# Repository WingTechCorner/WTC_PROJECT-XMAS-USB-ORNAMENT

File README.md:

# Wing's XMAS Ornament

** ISSUE - Design Seems To produce non-working unit. Investigating... **

* Something for the holidays.
* Made using SMT/SMD components so most/all parts on one side.
* Added header pins on revrse side for adding batteries or different UART(s).
* Added USB-A PCB top to allow plugging into a laptop or computer USB port or to power with a USB-A extension cable.

# JLCPCB Holiday Contest Entry

This is a project I'm also submitting to the [JLCPCB.com](http://www.jlcpcb.com) Holiday Contest!

* http://www.jlcpcb.com

# Hardware

## Components

* CH340G USB-to-TTL interface chip
* AMS1117-3v3 linear voltage regulator
* QMA7981 IMU in I2C mode
* STM32F030F4 - Arm M0 MCU

## STM32 

* 12Mhz External OSC
* Boot0 - CH340G's CTS (pin 9) (pulldown via 4.7K, but can be brought HIGH by CH340G by toggling CTS)

### I2C 

* PA9  - I2C SCL (connects to QMA7981's SCL)
* PA10 - I2C SDA (connects to QMA7981's SDX)
* PB1  - Motion Interrupt Signal ( connects to QMA7981's INT2 )

### UART

* PA2  - UART-TX (connects to CH340G's RX)
* PA3  - UART-RD (connects to CH340G's TX)

### LED Driving Lines

* PA0  - A (CharliePlexed LED Lines)
* PA1  - B (CharliePlexed LED Lines)
* PA4  - C (CharliePlexed LED Lines)
* PA5  - D (CharliePlexed LED Lines)
* PA6  - E (CharliePlexed LED Lines)
* PA7  - F (CharliePlexed LED Lines)
* PA13 - G (CharliePlexed LED Lines)
* PA14 - H (CharliePlexed LED Lines)

## QMA7981

* AD0  - Sets address. Routed to GND for 0. 0x12H
* INT2 - Interrupt signal output. Routed to PB1 on MCU

## CH340G

* TXD  - To MCU RXD
* RXD  - To MCU TXD
* CTS  - To MCU BOOT0 for boot mode selector
* 12Mhz External OSC

# Software

## Building & Installing Arduino Code
The code is setup as a `platformio` project. To build:

```bash
# To compile/build
pio run

# To upload (Note, assumes serial upload)
pio run --target=upload
```

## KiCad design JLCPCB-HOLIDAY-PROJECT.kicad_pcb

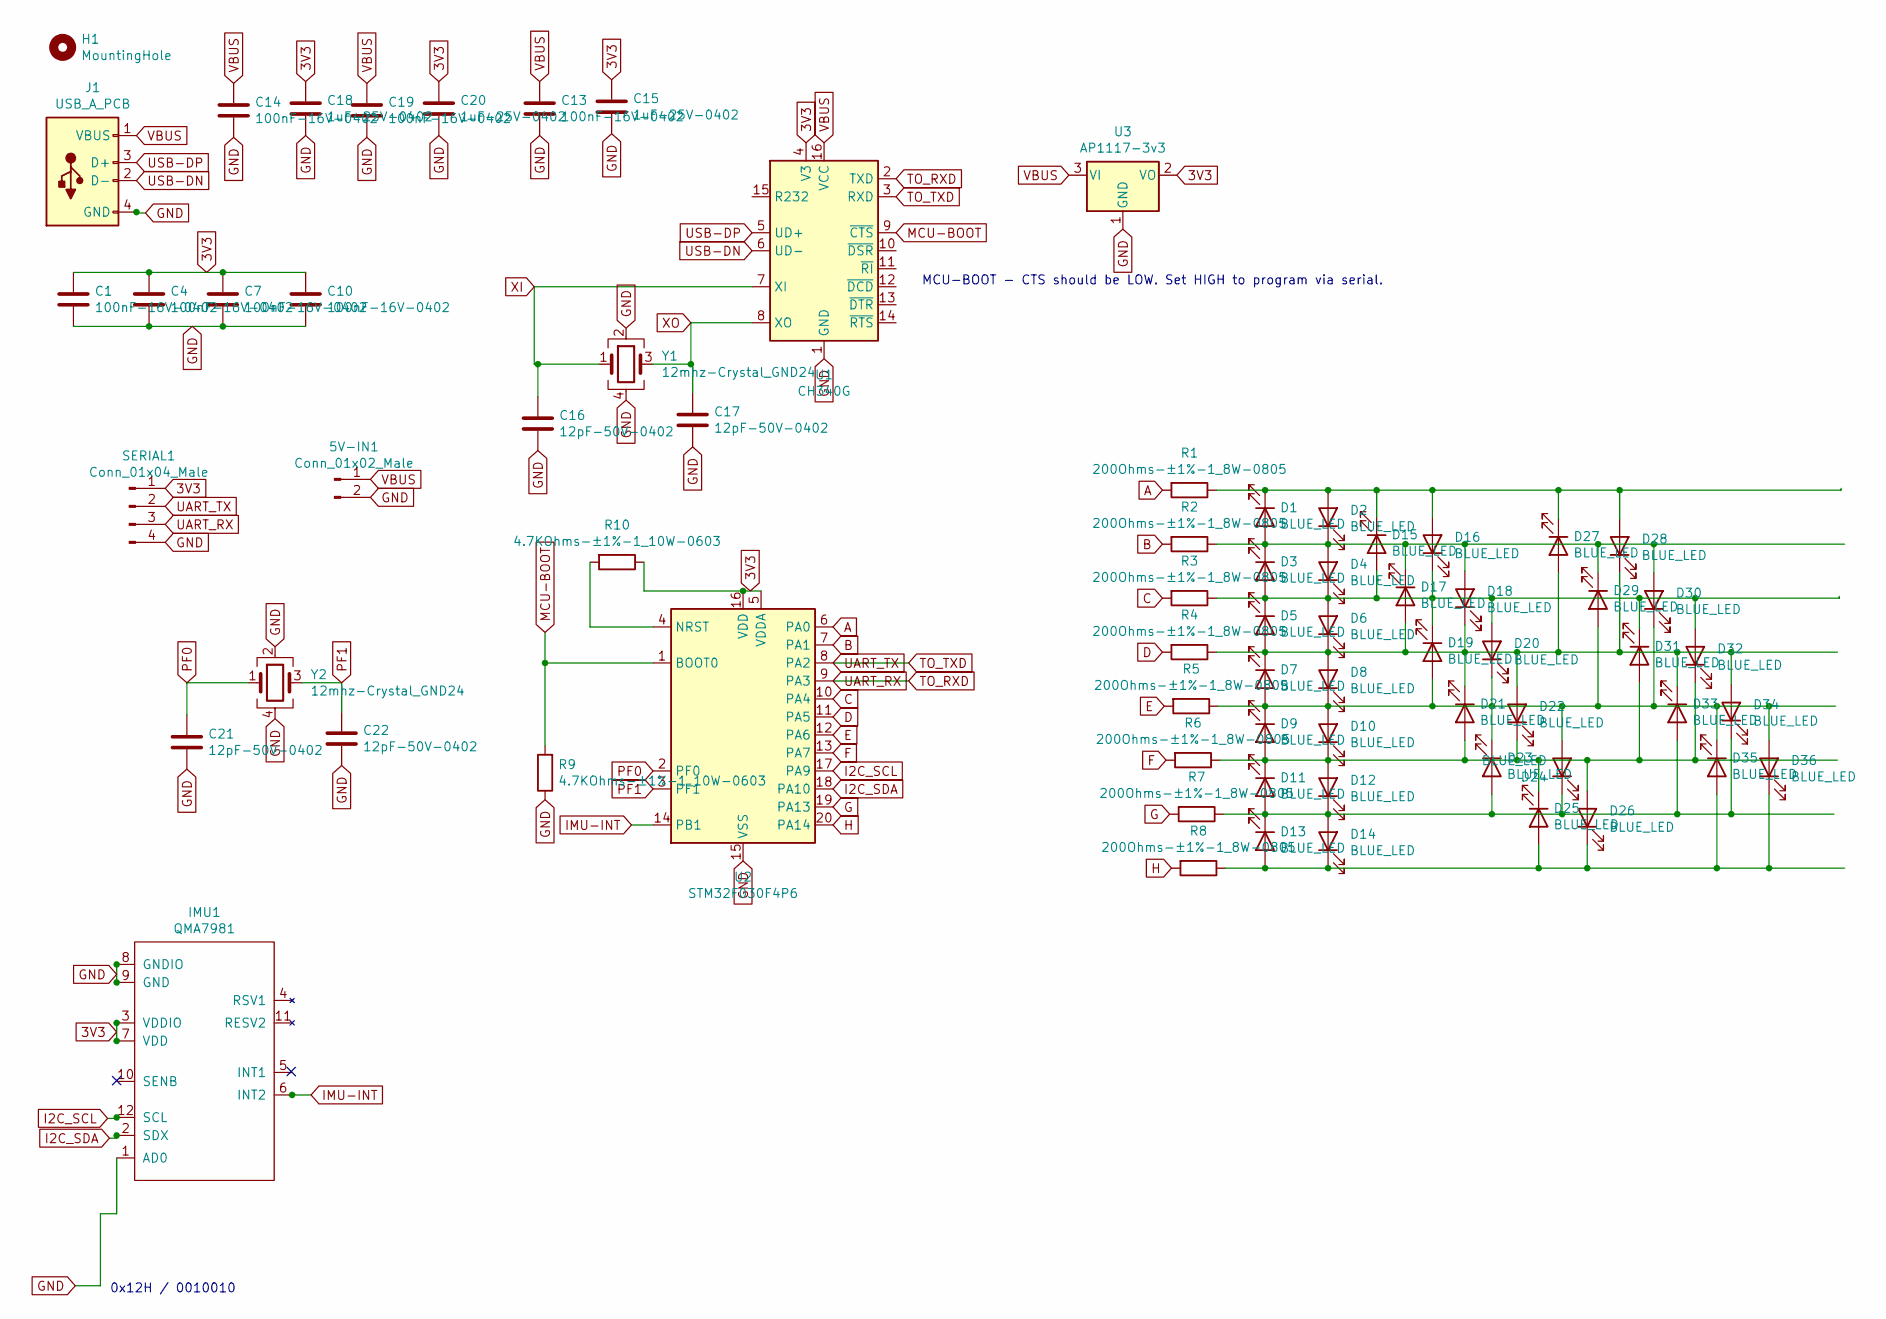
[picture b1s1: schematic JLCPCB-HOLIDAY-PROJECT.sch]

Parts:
5V-IN1: Conn_01x02_Male; PinHeader_1x02_P2.54mm_Vertical
C1, C4, C7, C10, C13, C14, C19: 100nF-16V-0402; C_0402_1005Metric; JLCPCB C1525
C15, C18, C20: 1uF-25V-0402; C_0402_1005Metric; JLCPCB C52923
C16, C17, C21, C22: 12pF-50V-0402; C_0402_1005Metric; JLCPCB C1547
D1, D2, D3, D4, D5, D6, D7, D8, D9, D10, D11, D12, D13, D14, D15, D16, D17, D18, D19, D20, D21, D22, D23, D24, D25, D26, D27, D28, D29, D30, D31, D32, D33, D34, D35, D36: BLUE_LED; D_0603_1608Metric; JLCPCB C72041
H1: MountingHole; MountingHole_2.2mm_M2
IMU1: QMA7981; LGA-12_2x2mm_P0.5mm; JLCPCBPART C457290
J1: USB_A_PCB; USB-A-PCB
R1, R2, R3, R4, R5, R6, R7, R8: 200Ohms-±1%-1_8W-0805; R_0805_2012Metric; JLCPCB C17540
R9, R10: 4.7KOhms-±1%-1_10W-0603; R_0603_1608Metric; JLCPCB C23162
SERIAL1: Conn_01x04_Male; PinHeader_1x04_P2.54mm_Vertical
U1: CH340G; SOIC-16_3.9x9.9mm_P1.27mm_JLC_ROTATED; JLCPCBPART C14267
U2: STM32F030F4P6; TSSOP-20_4.4x6.5mm_P0.65mm; JLCPCBPART C32908
U3: AP1117-3v3; SOT-223-3_TabPin2; JLCPCB C6186
Y1, Y2: 12mhz-Crystal_GND24; Crystal_SMD_TXC_7M-4Pin_3.2x2.5mm; JLCPCBPART C9002

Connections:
3V3: C1.1, C4.1, C7.1, C10.1, C15.1, C18.1, C20.1, IMU1.3 (VDDIO), IMU1.7 (VDD), R10.1, SERIAL1.1, U1.4 (V3), U2.5 (VDDA), U2.16 (VDD), U3.2 (VO)
A: R1.2, U2.6 (PA0)
B: R2.2, U2.7 (PA1)
C: R3.2, U2.10 (PA4)
D: R4.2, U2.11 (PA5)
E: R5.2, U2.12 (PA6)
F: R6.2, U2.13 (PA7)
G: R7.2, U2.19 (PA13)
GND: 5V-IN1.2, C1.2, C4.2, C7.2, C10.2, C13.2, C14.2, C15.2, C16.2, C17.2, C18.2, C19.2, C20.2, C21.2, C22.2, IMU1.1 (AD0), IMU1.8 (GNDIO), IMU1.9 (GND), J1.4 (GND), R9.1, SERIAL1.4, U1.1 (GND), U2.15 (VSS), U3.1 (GND), Y1.2, Y1.4, Y2.2, Y2.4
H: R8.2, U2.20 (PA14)
I2C_SCL: IMU1.12 (SCL), U2.17 (PA9)
I2C_SDA: IMU1.2 (SDX), U2.18 (PA10)
IMU-INT: IMU1.6 (INT2), U2.14 (PB1)
MCU-BOOT: R9.2, U1.9 (~CTS), U2.1 (BOOT0)
unnamed: D1.1 (K), D2.2 (A), D15.1 (K), D16.2 (A), D27.1 (K), D28.2 (A), R1.1
unnamed: D1.2 (A), D2.1 (K), D3.1 (K), D4.2 (A), D17.1 (K), D18.2 (A), D29.1 (K), D30.2 (A), R2.1
unnamed: D9.2 (A), D10.1 (K), D11.1 (K), D12.2 (A), D21.2 (A), D22.1 (K), D25.1 (K), D26.2 (A), D31.2 (A), D32.1 (K), R6.1
unnamed: D7.2 (A), D8.1 (K), D9.1 (K), D10.2 (A), D19.2 (A), D20.1 (K), D23.1 (K), D24.2 (A), D29.2 (A), D30.1 (K), D35.1 (K), D36.2 (A), R5.1
unnamed: D11.2 (A), D12.1 (K), D13.1 (K), D14.2 (A), D23.2 (A), D24.1 (K), D33.2 (A), D34.1 (K), R7.1
unnamed: D13.2 (A), D14.1 (K), D25.2 (A), D26.1 (K), D35.2 (A), D36.1 (K), R8.1
unnamed: D3.2 (A), D4.1 (K), D5.1 (K), D6.2 (A), D15.2 (A), D16.1 (K), D19.1 (K), D20.2 (A), D31.1 (K), D32.2 (A), R3.1
unnamed: D5.2 (A), D6.1 (K), D7.1 (K), D8.2 (A), D17.2 (A), D18.1 (K), D21.1 (K), D22.2 (A), D27.2 (A), D28.1 (K), D33.1 (K), D34.2 (A), R4.1
unnamed: R10.2, U2.4 (NRST)
PF0: C21.1, U2.2 (PF0), Y2.1
PF1: C22.1, U2.3 (PF1), Y2.3
TO_RXD: SERIAL1.3, U1.2 (TXD), U2.9 (PA3)
TO_TXD: SERIAL1.2, U1.3 (RXD), U2.8 (PA2)
USB-DN: J1.2 (D-), U1.6 (UD-)
USB-DP: J1.3 (D+), U1.5 (UD+)
VBUS: 5V-IN1.1, C13.1, C14.1, C19.1, J1.1 (VBUS), U1.16 (VCC), U3.3 (VI)
XI: C16.1, U1.7 (XI), Y1.1
XO: C17.1, U1.8 (XO), Y1.3

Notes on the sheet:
MCU-BOOT - CTS should be LOW. Set HIGH to program via serial.
0x12H / 0010010

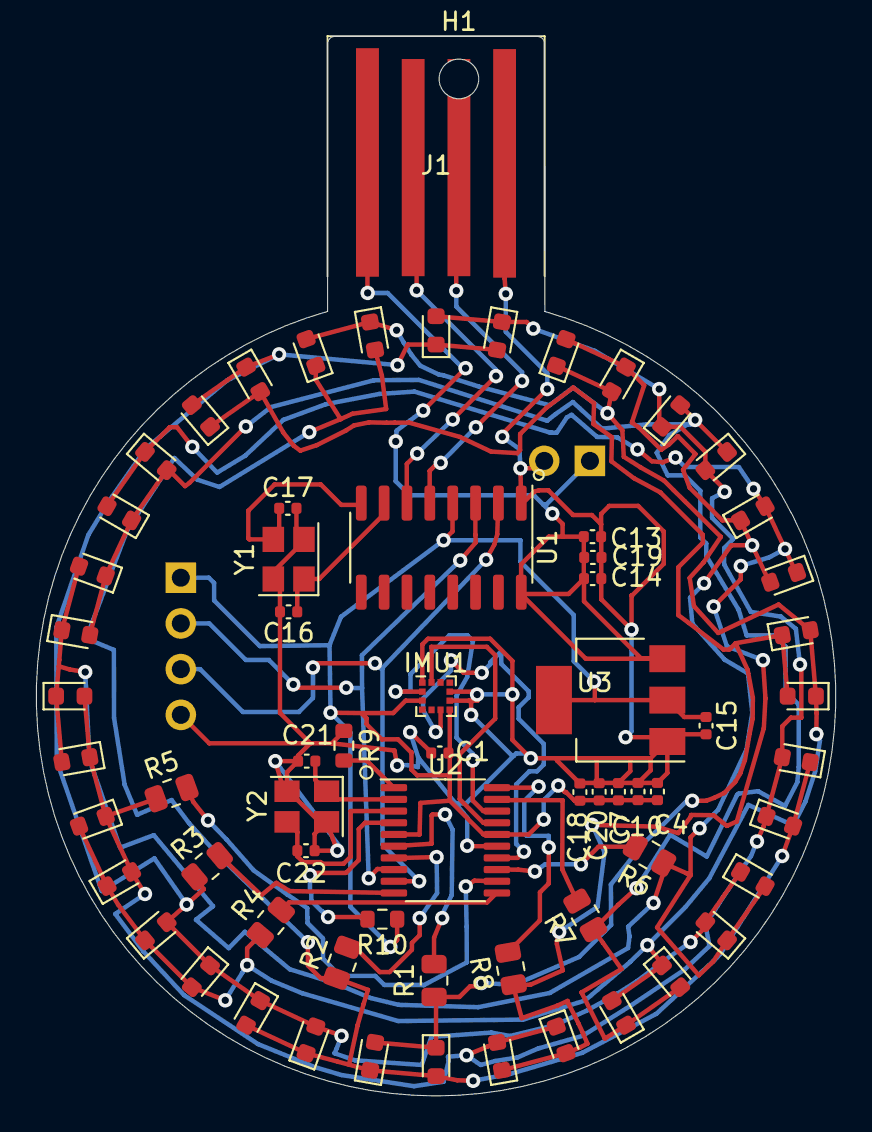
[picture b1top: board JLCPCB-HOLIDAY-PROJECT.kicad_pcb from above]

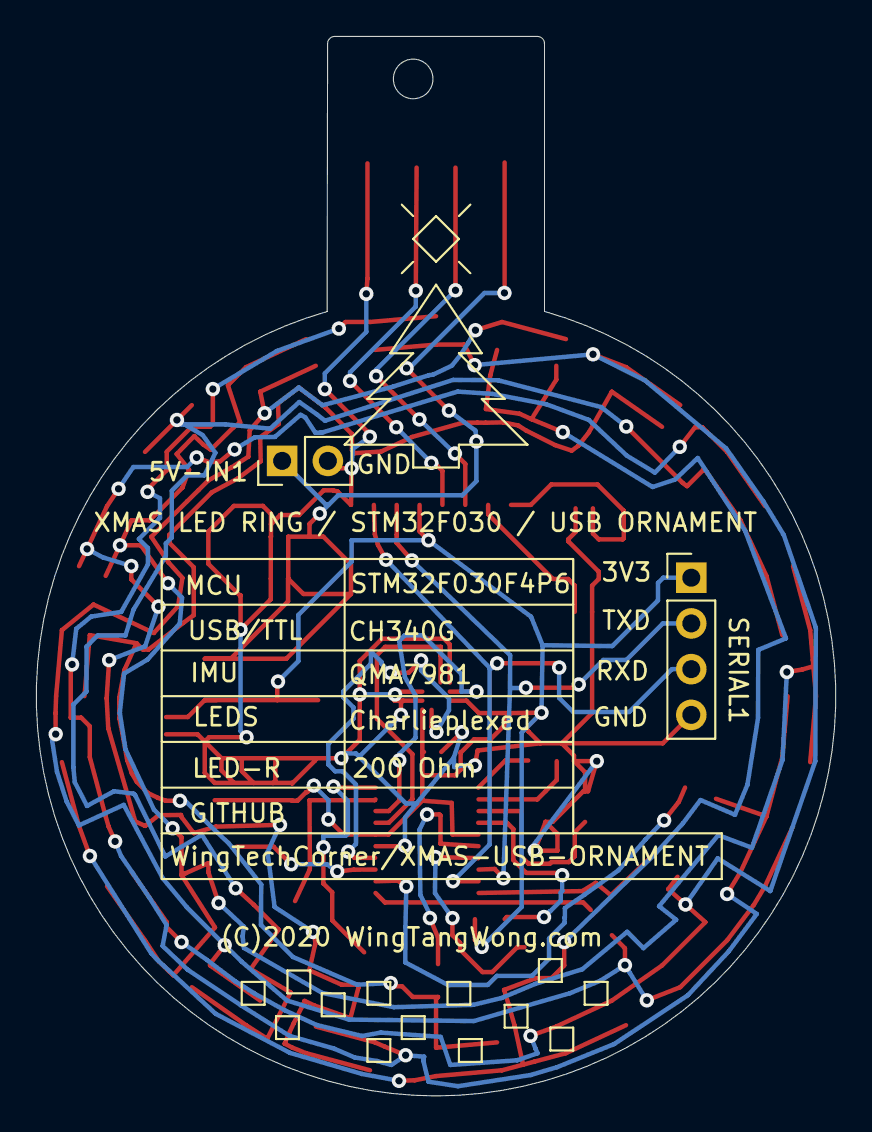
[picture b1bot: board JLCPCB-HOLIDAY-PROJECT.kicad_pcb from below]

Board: 2 copper layers, 44.4 x 58.9 mm, 70 parts (2 on the bottom side), 32 nets.

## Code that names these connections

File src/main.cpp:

/* ==================== ==================== ==================== ==================== 
 *  Wing Tang Wong's XMAS USB ORNAMENT Lighting Program
 *  ©2020 Wing Tang Wong
 * ==================== ==================== ==================== ==================== 
 *
 *  Code to control the hardware design of STM32F030F4 
 *  attached to 36 LED(s) in a charlieplexed configuration.
 *
 *  Communication with the MCU can be done via:
 *  - 4 pin UART header
 *  - USB serial via onboard CH340G
 *
 *  Power can be supplied via:
 *  - USB 5V
 *  - 5-12V via 2 pin
 *  - 3v3 via UART header
 *
 */

/* ==================== ==================== ==================== ==================== 
 *  Basic Arduino Boilerplate and libraries
 * ==================== ==================== ==================== ==================== 
 *
 * - Arduino.h  For basic Arduino stuff
 * - Wire.h     Mainly for I2C communication with the QMA7981 IMU
 *
 *
 */
#include <Arduino.h>
#include <Wire.h>

/* ==================== ==================== ==================== ==================== 
 * Global States of LED(s)
 * ==================== ==================== ==================== ==================== 
 * All default to zero
 * 0 = OFF
 * 128 = MAX ON
 */
uint8_t LED_STATE[36] = {0,0,0,0,0,0,0,0,0,0,0,0,0,0,0,0,0,0,0,0,0,0,0,0,0,0,0,0,0,0,0,0,0,0,0,0};
uint8_t LED_COUNTER[36] = {0,0,0,0,0,0,0,0,0,0,0,0,0,0,0,0,0,0,0,0,0,0,0,0,0,0,0,0,0,0,0,0,0,0,0,0};

/* ==================== ==================== ==================== ==================== 
 * Mapping pins of STM32 to rows
 * ==================== ==================== ==================== ==================== 
 *
 * PA0 - A (CharliePlexed LED Lines)
 * PA1 - B (CharliePlexed LED Lines)
 * PA4 - C (CharliePlexed LED Lines)
 * PA5 - D (CharliePlexed LED Lines)
 * PA6 - E (CharliePlexed LED Lines)
 * PA7 - F (CharliePlexed LED Lines)
 * PA13 - G (CharliePlexed LED Lines)
 * PA14 - H (CharliePlexed LED Lines)
 */
uint8_t ROW_PIN[8] = { PA0, PA1, PA4, PA5, PA6, PA7, PA13, PA14 };


/*
 * ==================== ==================== ==================== ==================== 
 * Charlie Plexing Map for LED1 through LED36
 * ==================== ==================== ==================== ==================== 
 *
 * 0 = LOW
 * 1 = HIGH
 * x = DONT CARE
 *
 * For LED(s) that do not conflict with one
 * another, it should be possible to light up
 * more than one LED at a time.
 *
 * D1  = A1, B0 , Cx , Dx , Ex , Fx , Gx , Hx
 * D2  = A0, B1 , Cx , Dx , Ex , Fx , Gx , Hx
 * D3  = Ax, B0 , C1 , Dx , Ex , Fx , Gx , Hx
 * D4  = Ax, B1 , C0 , Dx , Ex , Fx , Gx , Hx
 * D5  = Ax, Bx , C0 , D1 , Ex , Fx , Gx , Hx
 * D6  = Ax, Bx , C1 , D0 , Ex , Fx , Gx , Hx
 * D7  = Ax, Bx , Cx , D0 , E1 , Fx , Gx , Hx
 * D8  = Ax, Bx , Cx , D1 , E0 , Fx , Gx , Hx
 * D9  = Ax, Bx , Cx , Dx , E0 , F1 , Gx , Hx
 * D10 = Ax, Bx , Cx , Dx , E1 , F0 , Gx , Hx
 * D11 = Ax, Bx , Cx , Dx , Ex , F0 , G1 , Hx
 * D12 = Ax, Bx , Cx , Dx , Ex , F1 , G0 , Hx
 * D13 = Ax, Bx , Cx , Dx , Ex , Fx , G0 , H1
 * D14 = Ax, Bx , Cx , Dx , Ex , Fx , G1 , H0
 *
 * D15 = A0, Bx , C1 , Dx , Ex , Fx , Gx , Hx
 * D16 = A1, Bx , C0 , Dx , Ex , Fx , Gx , Hx
 * D17 = Ax, B0 , Cx , D1 , Ex , Fx , Gx , Hx
 * D18 = Ax, B1 , Cx , D0 , Ex , Fx , Gx , Hx
 * D19 = Ax, Bx , C0 , Dx , E1 , Fx , Gx , Hx
 * D20 = Ax, Bx , C1 , Dx , E0 , Fx , Gx , Hx
 * D21 = Ax, Bx , Cx , D0 , Ex , F1 , Gx , Hx
 * D22 = Ax, Bx , Cx , D1 , Ex , F0 , Gx , Hx
 * D23 = Ax, Bx , Cx , Dx , E0 , Fx , G1 , Hx
 * D24 = Ax, Bx , Cx , Dx , E1 , Fx , G0 , Hx
 * D25 = Ax, Bx , Cx , Dx , Ex , F0 , Gx , H1
 * D26 = Ax, Bx , Cx , Dx , Ex , F1 , Gx , H0
 *
 * D27 = A0, Bx , Cx , D1 , Ex , Fx , Gx , Hx
 * D28 = A1, Bx , Cx , D0 , Ex , Fx , Gx , Hx
 * D29 = Ax, B0 , Cx , Dx , E1 , Fx , Gx , Hx
 * D30 = Ax, B1 , Cx , Dx , E0 , Fx , Gx , Hx
 * D31 = Ax, Bx , C0 , Dx , Ex , F1 , Gx , Hx
 * D32 = Ax, Bx , C1 , Dx , Ex , F0 , Gx , Hx
 * D33 = Ax, Bx , Cx , D0 , Ex , Fx , G1 , Hx
 * D34 = Ax, Bx , Cx , D1 , Ex , Fx , G0 , Hx
 * D35 = Ax, Bx , Cx , Dx , E0 , Fx , Gx , H1
 * D36 = Ax, Bx , Cx , Dx , E1 , Fx , Gx , H0
 *
 */
uint8_t LED_PINS[36][8] = {
  { 1, 0 , 0 , 0 , 0 , 0 , 0 , 0 },
  { 0, 1 , 0 , 0 , 0 , 0 , 0 , 0 },
  { 0, 0 , 1 , 0 , 0 , 0 , 0 , 0 },
  { 0, 1 , 0 , 0 , 0 , 0 , 0 , 0 },
  { 0, 0 , 0 , 1 , 0 , 0 , 0 , 0 },
  { 0, 0 , 1 , 0 , 0 , 0 , 0 , 0 },
  { 0, 0 , 0 , 0 , 1 , 0 , 0 , 0 },
  { 0, 0 , 0 , 1 , 0 , 0 , 0 , 0 },
  { 0, 0 , 0 , 0 , 0 , 1 , 0 , 0 },
  { 0, 0 , 0 , 0 , 1 , 0 , 0 , 0 },
  { 0, 0 , 0 , 0 , 0 , 0 , 1 , 0 },
  { 0, 0 , 0 , 0 , 0 , 1 , 0 , 0 },
  { 0, 0 , 0 , 0 , 0 , 0 , 0 , 1 },
  { 0, 0 , 0 , 0 , 0 , 0 , 1 , 0 },
  { 0, 0 , 1 , 0 , 0 , 0 , 0 , 0 },
  { 1, 0 , 0 , 0 , 0 , 0 , 0 , 0 },
  { 0, 0 , 0 , 1 , 0 , 0 , 0 , 0 },
  { 0, 1 , 0 , 0 , 0 , 0 , 0 , 0 },
  { 0, 0 , 0 , 0 , 1 , 0 , 0 , 0 },
  { 0, 0 , 1 , 0 , 0 , 0 , 0 , 0 },
  { 0, 0 , 0 , 0 , 0 , 1 , 0 , 0 },
  { 0, 0 , 0 , 1 , 0 , 0 , 0 , 0 },
  { 0, 0 , 0 , 0 , 0 , 0 , 1 , 0 },
  { 0, 0 , 0 , 0 , 1 , 0 , 0 , 0 },
  { 0, 0 , 0 , 0 , 0 , 0 , 0 , 1 },
  { 0, 0 , 0 , 0 , 0 , 1 , 0 , 0 },
  { 0, 0 , 0 , 1 , 0 , 0 , 0 , 0 },
  { 1, 0 , 0 , 0 , 0 , 0 , 0 , 0 },
  { 0, 0 , 0 , 0 , 1 , 0 , 0 , 0 },
  { 0, 1 , 0 , 0 , 0 , 0 , 0 , 0 },
  { 0, 0 , 0 , 0 , 0 , 1 , 0 , 0 },
  { 0, 0 , 1 , 0 , 0 , 0 , 0 , 0 },
  { 0, 0 , 0 , 0 , 0 , 0 , 1 , 0 },
  { 0, 0 , 0 , 1 , 0 , 0 , 0 , 0 },
  { 0, 0 , 0 , 0 , 0 , 0 , 0 , 1 },
  { 0, 0 , 0 , 0 , 1 , 0 , 0 , 0 } 
};




/* 
 * ==================== ==================== ==================== ==================== 
 * Interrupt related variables. 
 * - Interrupt line is from the IMU
 * ==================== ==================== ==================== ==================== 
 */

uint8_t imuPIN = PB1;
volatile int imuSTATE = LOW;

/* 
 * ==================== ==================== ==================== ==================== 
 * Various variables For main application
 * ==================== ==================== ==================== ==================== 
 */

uint32_t ts_delta =0;
uint32_t ts_tick  =5000;
uint32_t ts_last  =0;
uint32_t ts_curr  =0;
uint8_t  active_led = 0;

/* 
 * ==================== ==================== ==================== ==================== 
 * Function declarations
 *
 * Sane folks probably just put this all into a 'main.h' file.... >_>
 * ==================== ==================== ==================== ==================== 
 */

void LED_ON( uint8_t led );
void LED_OFF( uint8_t led);
void LED_SET( uint8_t led, uint8_t val );
void DISPLAY_LED(uint8_t led);
void LED_DISPLAY();
void LED_TICK();
void IMU_SERVICE_UP();
void IMU_SERVICE_DOWN();


/* 
 * ==================== ==================== ==================== ==================== 
 * Setup
 * ==================== ==================== ==================== ==================== 
 */
void setup() {
  // Setup an interrupt for the IMU (PB1)
  //
  attachInterrupt(digitalPinToInterrupt(imuPIN),IMU_SERVICE_UP,RISING);
  attachInterrupt(digitalPinToInterrupt(imuPIN),IMU_SERVICE_DOWN,FALLING);

  // Load up some values for the interval timers
  ts_last=micros();
  ts_curr=micros();
  ts_delta=ts_curr - ts_last;
};

/* 
 * ==================== ==================== ==================== ==================== 
 * Main Loop
 * ==================== ==================== ==================== ==================== 
 */

void loop() {
  ts_curr=micros();

  // After a duration of ts_tick, update which LED gets lit
  if ( ( ts_curr - ts_last ) > ts_tick ) {
    ts_last = ts_curr;    
    LED_OFF(active_led);
    active_led += 1;
    LED_ON(active_led);
  };

  LED_TICK();
  LED_DISPLAY();
};

/* 
 * ==================== ==================== ==================== ==================== 
 * functions to set LED state
 * ==================== ==================== ==================== ==================== 
 *
 * General idea... the value assigned to the state of the LED is the target that needs
 * to be hit to shut the light off.
 *
 * However, only one light should ever be on at one time. 
 */

void LED_ON( uint8_t led) {
  LED_STATE[led]=128;  
};

void LED_OFF( uint8_t led){
  LED_STATE[led]=0;
};

void LED_SET( uint8_t led, uint8_t val = 128) {
  if ( val >= 128 ) {
    LED_STATE[led]=128;
  } else {
    LED_STATE[led]=val;
  };
};

void LED_TICK() {
  for( uint8_t i=0; i<36; i++ ) {
    LED_COUNTER[i] += 1;
    if ( LED_COUNTER[i] > LED_STATE[i] ) { LED_COUNTER[i]=0; };
  };
};

void DISPLAY_LED(uint8_t led = 0) {
  if ( led < 36 ) {
    for( uint8_t row = 0; row < 8; row++ ) {
      digitalWrite( ROW_PIN[row], LED_PINS[led][row] );
    };
  }; 
};


void LED_DISPLAY() {
  for( uint8_t i=0; i<36; i++ ) {
    if ( LED_COUNTER[i] <= LED_STATE[i] ) {
      DISPLAY_LED(i);
    };
  };
};


/* 
 * ==================== ==================== ==================== ==================== 
 * ISR Handling Function from IMU
 * ==================== ==================== ==================== ==================== 
 */
void IMU_SERVICE_UP() {
  imuSTATE = HIGH;
};

void IMU_SERVICE_DOWN() {
  imuSTATE = LOW;
};

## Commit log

2020-11-04 80% of the way done
2020-11-04 Makefile
2020-11-04 Adding ignore file
2020-11-04 Adding silkscreen text on back
2020-11-04 Added more text notes
2020-11-04 Sync
2020-11-04 Removing backup files
2020-11-05 Adding readme
2020-11-05 Updated traces to add interrupt return, address set to 0, and boot/nrst for the mcu
2020-11-05 Update Adding mention that this is being submitted for the JLCPCB Holiday Contest Update README.md Added images Resized jpeg Updated readme Moving HW files into Hardware. Adding Platform IO bits for 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
2020-11-05 Cleanup
2020-11-05 Added some template functions
2020-11-06 Added more routines for handling LED state counting, displaying LED(s), and putting the rows/pins into an array for easy referening.
2020-11-06 Updated interrupt into separate up and down functions.
2020-11-06 moved images
2020-11-06 Added STM32 pinouts and updated README.me
2020-11-06 Added a simple loop to increment through the LED(s) turning off the previous LED.
2020-11-19 Found error with board. Don't use yet.

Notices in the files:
JLCPCB-HOLIDAY-PROJECT.kicad_pcb:
(C)2020 WingTangWong.com
